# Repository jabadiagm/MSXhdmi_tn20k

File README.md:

# MSXhdmi_tn20k
Adaptador hdmi para MSX1 / MSX1 hdmi adapter

Permite conectar un MSX de primera generación a un monitor convencional. La lógica está contenida en una Tang Nano 20K que se encarga de reproducir imagen (vdp) y sonido (psg + fm + scc). Parcialmente compatible con el software MSX2. Adaptación del vdp V9958 escrita por [lfantoniosi](https://github.com/lfantoniosi).

Configuración de sofarun para utilizar scc externa:

[https://www.msx.org/forum/msx-talk/hardware/report-konami-scc-standalone-with-sofarun](https://www.msx.org/forum/msx-talk/hardware/report-konami-scc-standalone-with-sofarun)

Allows the conection between a first generation MSX and a conventional monitor. Logic is contained in a Tang Nano 20K which is in charge of playing picture (vdp) and sound (psg + fm + scc). Partially compatible with MSX2 software. V9958 adapted by [lfantoniosi](https://github.com/lfantoniosi).

sofarun config using external scc:

[https://www.msx.org/forum/msx-talk/hardware/report-konami-scc-standalone-with-sofarun](https://www.msx.org/forum/msx-talk/hardware/report-konami-scc-standalone-with-sofarun)

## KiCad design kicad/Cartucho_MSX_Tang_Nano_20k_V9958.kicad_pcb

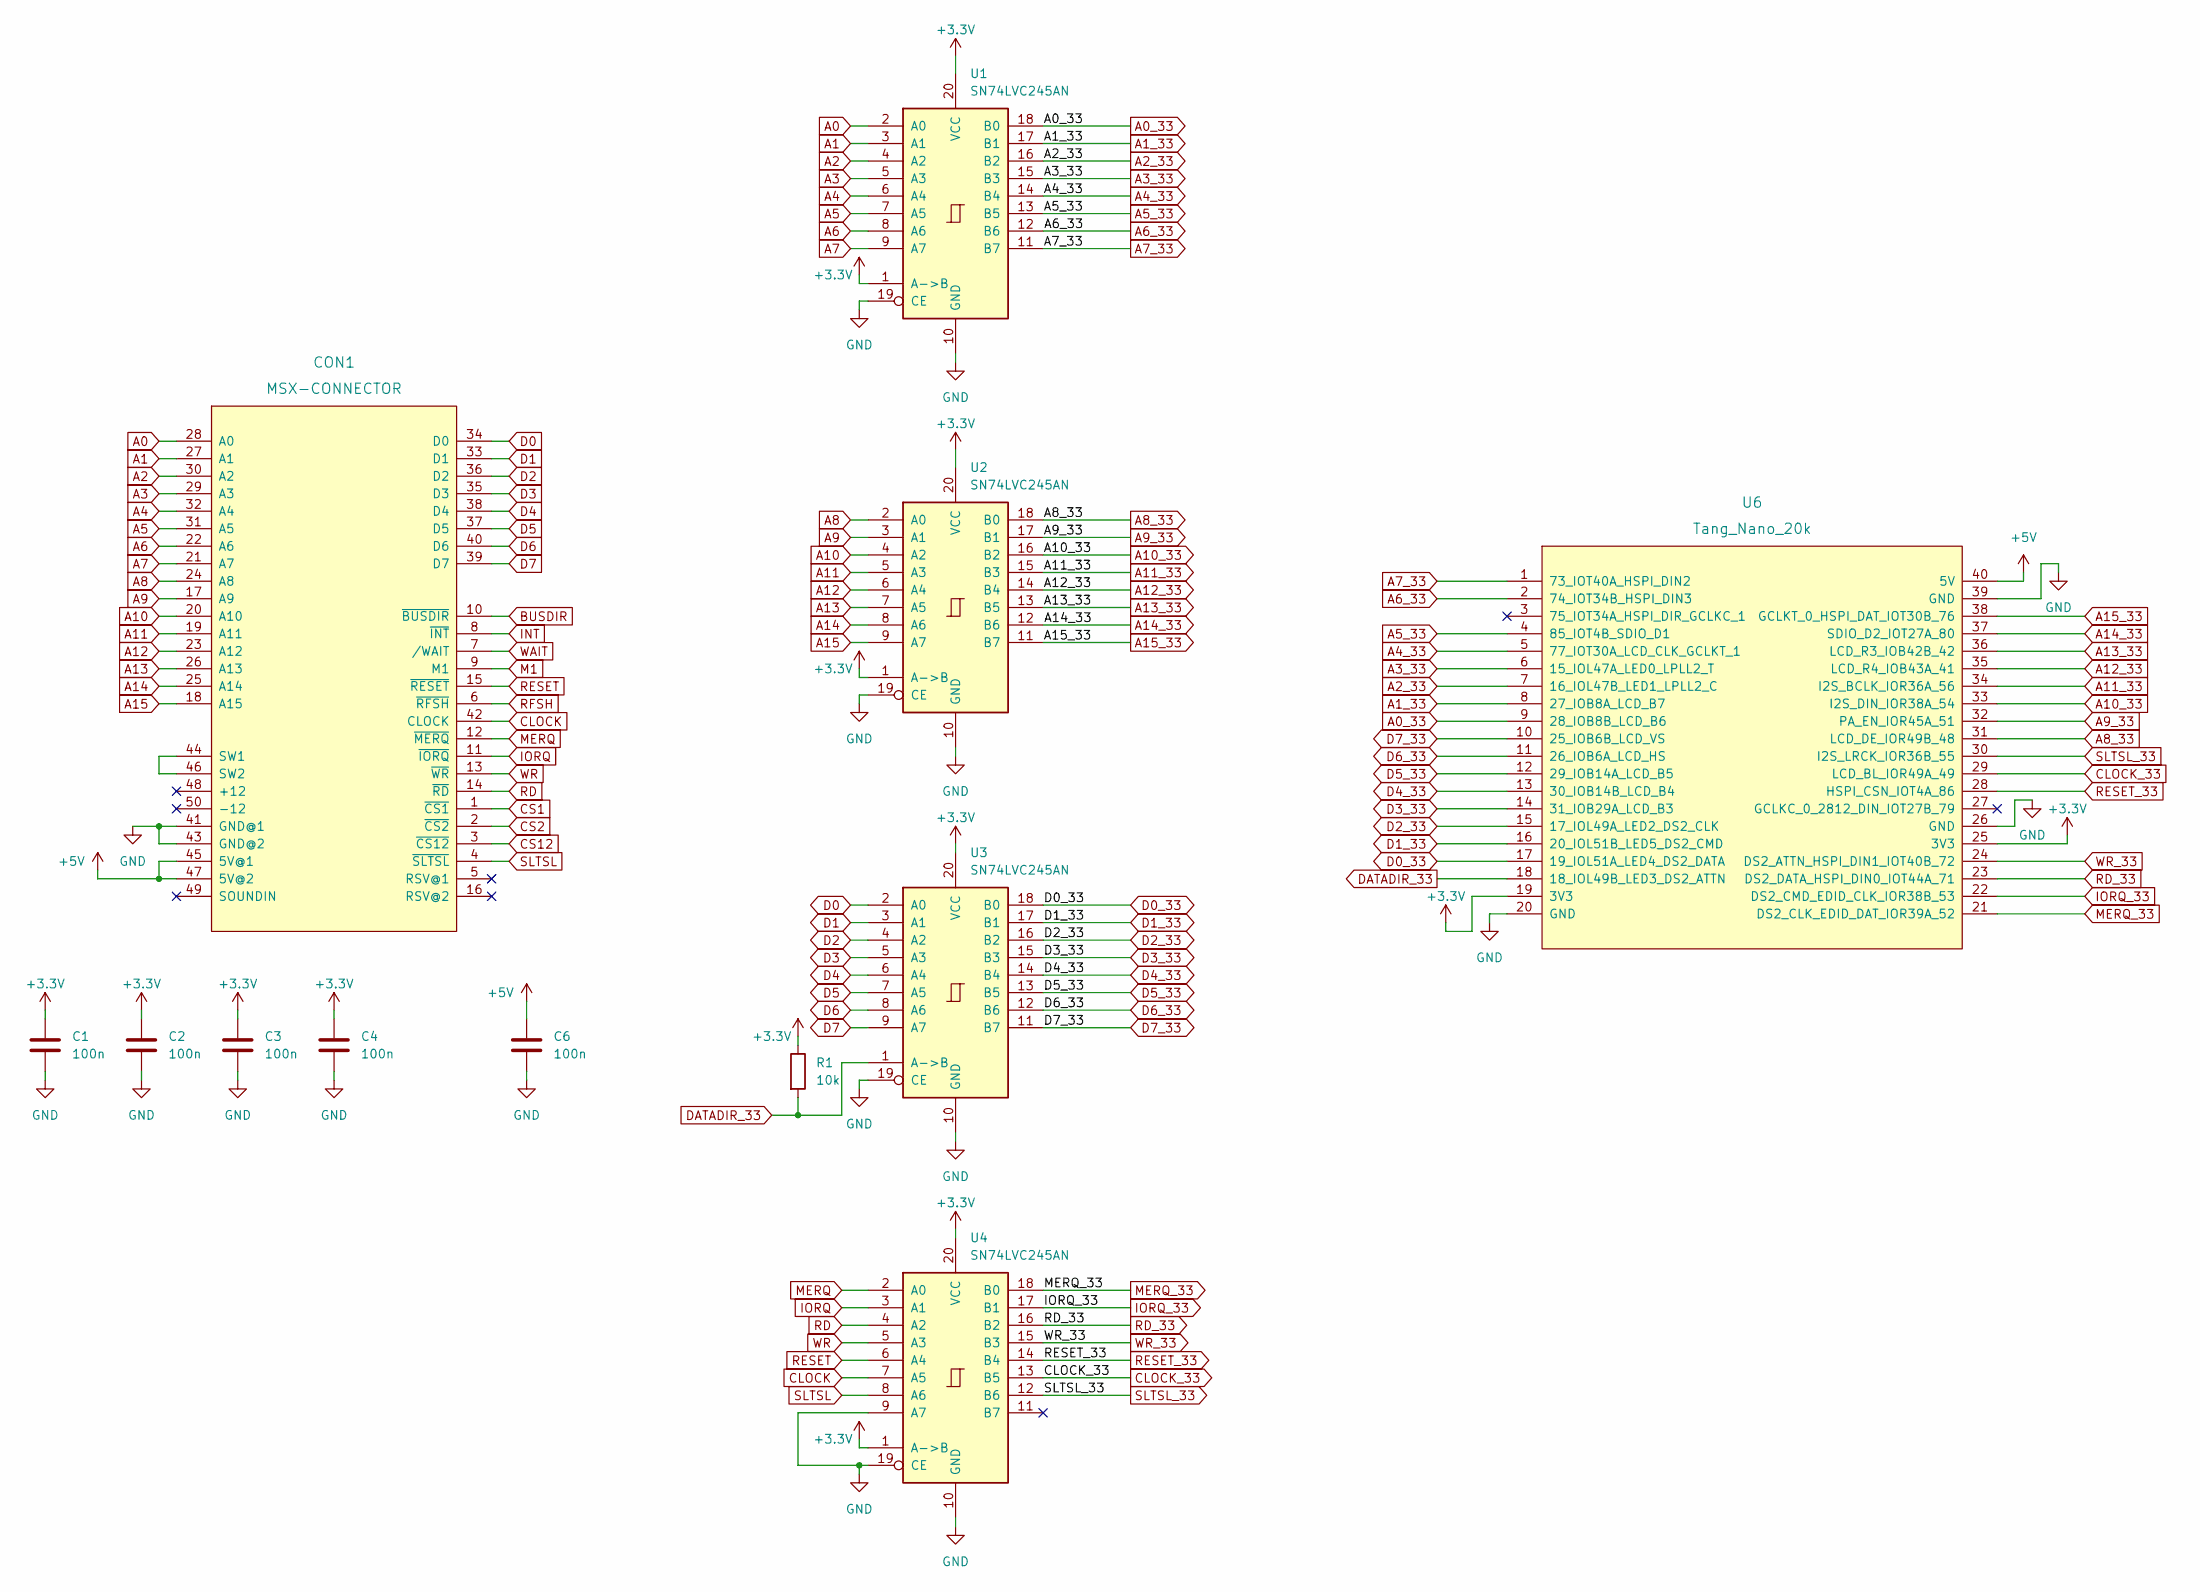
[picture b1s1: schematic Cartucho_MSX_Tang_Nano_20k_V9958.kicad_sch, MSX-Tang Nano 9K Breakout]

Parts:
C1, C2, C3, C4, C6: 100n; C_Disc_D4.3mm_W1.9mm_P5.00mm
CON1: MSX-CONNECTOR; CARTRIDGE_MSX
R1: 10k; R_Axial_DIN0207_L6.3mm_D2.5mm_P7.62mm_Horizontal
U1, U2, U3, U4: SN74LVC245AN; DIP-20_W7.62mm_LongPads
U6: Tang_Nano_20k

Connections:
+3.3V: C1.1, C2.1, C3.1, C4.1, R1.1, U1.1 (A->B), U1.20 (VCC), U2.1 (A->B), U2.20 (VCC), U3.20 (VCC), U4.1 (A->B), U4.20 (VCC), U6.19 (3V3), U6.25 (3V3)
+5V: C6.1, CON1.45 (5V@1), CON1.47 (5V@2), U6.40 (5V)
A0: CON1.28 (A0), U1.2 (A0)
A0_33: U1.18 (B0), U6.9 (28_IOB8B_LCD_B6)
A1: CON1.27 (A1), U1.3 (A1)
A1_33: U1.17 (B1), U6.8 (27_IOB8A_LCD_B7)
A2: CON1.30 (A2), U1.4 (A2)
A2_33: U1.16 (B2), U6.7 (16_IOL47B_LED1_LPLL2_C)
A3: CON1.29 (A3), U1.5 (A3)
A3_33: U1.15 (B3), U6.6 (15_IOL47A_LED0_LPLL2_T)
A4: CON1.32 (A4), U1.6 (A4)
A4_33: U1.14 (B4), U6.5 (77_IOT30A_LCD_CLK_GCLKT_1)
A5: CON1.31 (A5), U1.7 (A5)
A5_33: U1.13 (B5), U6.4 (85_IOT4B_SDIO_D1)
A6: CON1.22 (A6), U1.8 (A6)
A6_33: U1.12 (B6), U6.2 (74_IOT34B_HSPI_DIN3)
A7: CON1.21 (A7), U1.9 (A7)
A7_33: U1.11 (B7), U6.1 (73_IOT40A_HSPI_DIN2)
A8: CON1.24 (A8), U2.2 (A0)
A8_33: U2.18 (B0), U6.31 (LCD_DE_IOR49B_48)
A9: CON1.17 (A9), U2.3 (A1)
A9_33: U2.17 (B1), U6.32 (PA_EN_IOR45A_51)
A10: CON1.20 (A10), U2.4 (A2)
A10_33: U2.16 (B2), U6.33 (I2S_DIN_IOR38A_54)
A11: CON1.19 (A11), U2.5 (A3)
A11_33: U2.15 (B3), U6.34 (I2S_BCLK_IOR36A_56)
A12: CON1.23 (A12), U2.6 (A4)
A12_33: U2.14 (B4), U6.35 (LCD_R4_IOB43A_41)
A13: CON1.26 (A13), U2.7 (A5)
A13_33: U2.13 (B5), U6.36 (LCD_R3_IOB42B_42)
A14: CON1.25 (A14), U2.8 (A6)
A14_33: U2.12 (B6), U6.37 (SDIO_D2_IOT27A_80)
A15: CON1.18 (A15), U2.9 (A7)
A15_33: U2.11 (B7), U6.38 (GCLKT_0_HSPI_DAT_IOT30B_76)
BUSDIR: CON1.10 (~BUSDIR)
CLOCK: CON1.42 (CLOCK), U4.7 (A5)
CLOCK_33: U4.13 (B5), U6.29 (LCD_BL_IOR49A_49)
CS1: CON1.1 (~CS1)
CS2: CON1.2 (~CS2)
CS12: CON1.3 (~CS12)
D0: CON1.34 (D0), U3.2 (A0)
D0_33: U3.18 (B0), U6.17 (19_IOL51A_LED4_DS2_DATA)
D1: CON1.33 (D1), U3.3 (A1)
D1_33: U3.17 (B1), U6.16 (20_IOL51B_LED5_DS2_CMD)
D2: CON1.36 (D2), U3.4 (A2)
D2_33: U3.16 (B2), U6.15 (17_IOL49A_LED2_DS2_CLK)
D3: CON1.35 (D3), U3.5 (A3)
D3_33: U3.15 (B3), U6.14 (31_IOB29A_LCD_B3)
D4: CON1.38 (D4), U3.6 (A4)
D4_33: U3.14 (B4), U6.13 (30_IOB14B_LCD_B4)
D5: CON1.37 (D5), U3.7 (A5)
D5_33: U3.13 (B5), U6.12 (29_IOB14A_LCD_B5)
D6: CON1.40 (D6), U3.8 (A6)
D6_33: U3.12 (B6), U6.11 (26_IOB6A_LCD_HS)
D7: CON1.39 (D7), U3.9 (A7)
D7_33: U3.11 (B7), U6.10 (25_IOB6B_LCD_VS)
DATADIR_33: R1.2, U3.1 (A->B), U6.18 (18_IOL49B_LED3_DS2_ATTN)
GND: C1.2, C2.2, C3.2, C4.2, C6.2, CON1.41 (GND@1), CON1.43 (GND@2), U1.10 (GND), U1.19 (CE), U2.10 (GND), U2.19 (CE), U3.10 (GND), U3.19 (CE), U4.9 (A7), U4.10 (GND), U4.19 (CE), U6.20 (GND), U6.26 (GND), U6.39 (GND)
INT: CON1.8 (~INT)
IORQ: CON1.11 (~IORQ), U4.3 (A1)
IORQ_33: U4.17 (B1), U6.22 (DS2_CMD_EDID_CLK_IOR38B_53)
M1: CON1.9 (M1)
MERQ: CON1.12 (~MERQ), U4.2 (A0)
MERQ_33: U4.18 (B0), U6.21 (DS2_CLK_EDID_DAT_IOR39A_52)
unnamed: CON1.44 (SW1), CON1.46 (SW2)
RD: CON1.14 (~RD), U4.4 (A2)
RD_33: U4.16 (B2), U6.23 (DS2_DATA_HSPI_DIN0_IOT44A_71)
RESET: CON1.15 (~RESET), U4.6 (A4)
RESET_33: U4.14 (B4), U6.28 (HSPI_CSN_IOT4A_86)
RFSH: CON1.6 (~RFSH)
SLTSL: CON1.4 (~SLTSL), U4.8 (A6)
SLTSL_33: U4.12 (B6), U6.30 (I2S_LRCK_IOR36B_55)
WAIT: CON1.7 (/WAIT)
WR: CON1.13 (~WR), U4.5 (A3)
WR_33: U4.15 (B3), U6.24 (DS2_ATTN_HSPI_DIN1_IOT40B_72)

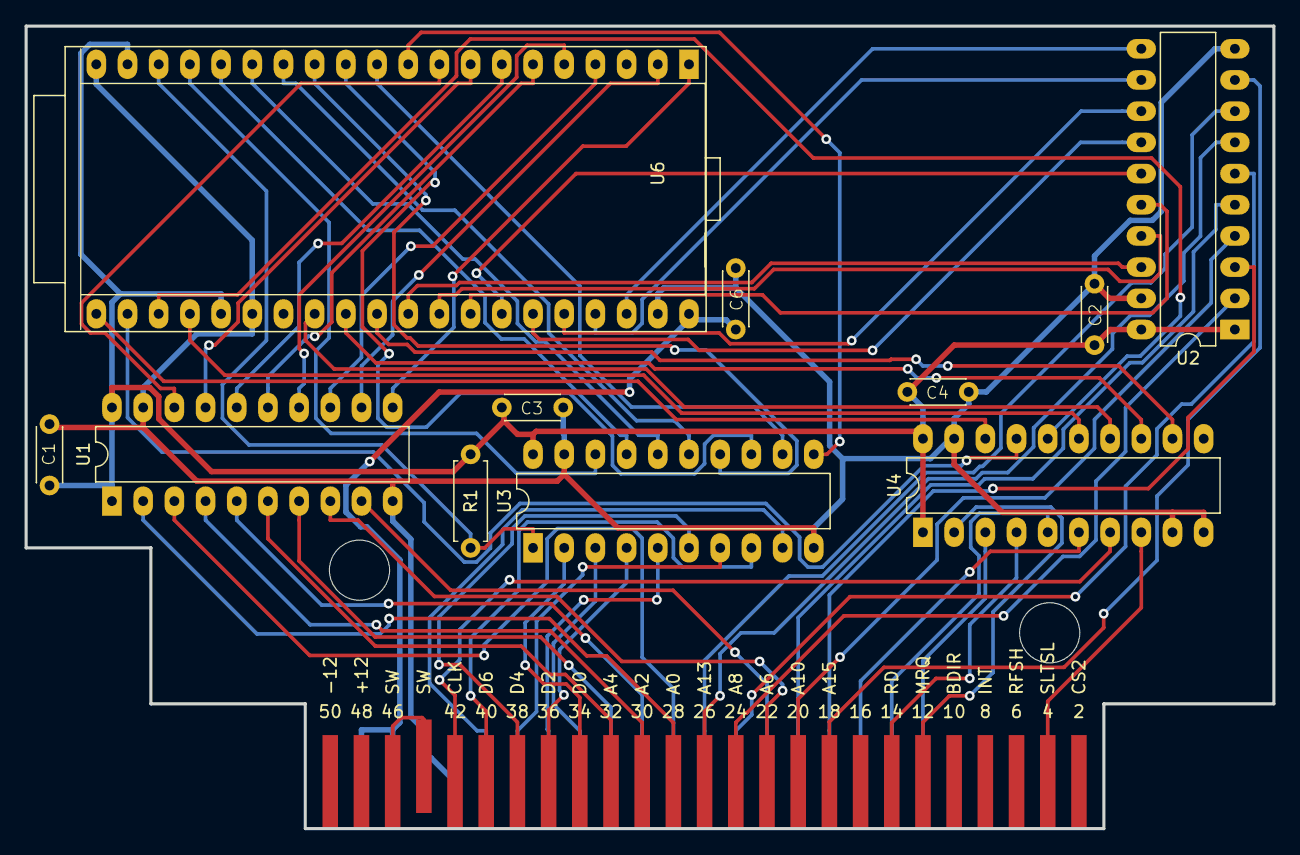
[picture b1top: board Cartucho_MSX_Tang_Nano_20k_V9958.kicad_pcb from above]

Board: 2 copper layers, 101.6 x 65.3 mm, 12 parts (0 on the bottom side), 67 nets.

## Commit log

2023-07-16 Inicial
2023-07-22 Cambiada distribución de pines Incluída rom FM Incluída pcb kicad
    -------------------------
    Updated pinout
    Included fm rom
    Included kicad pcb
2023-07-26 Corregido bug de dirección de bus
    ---------------------------------
    Fixed bug with busdir
2023-08-13 Añadido soporte básico para sonido scc
    ------------------------------------
    Included basic support for scc sound
